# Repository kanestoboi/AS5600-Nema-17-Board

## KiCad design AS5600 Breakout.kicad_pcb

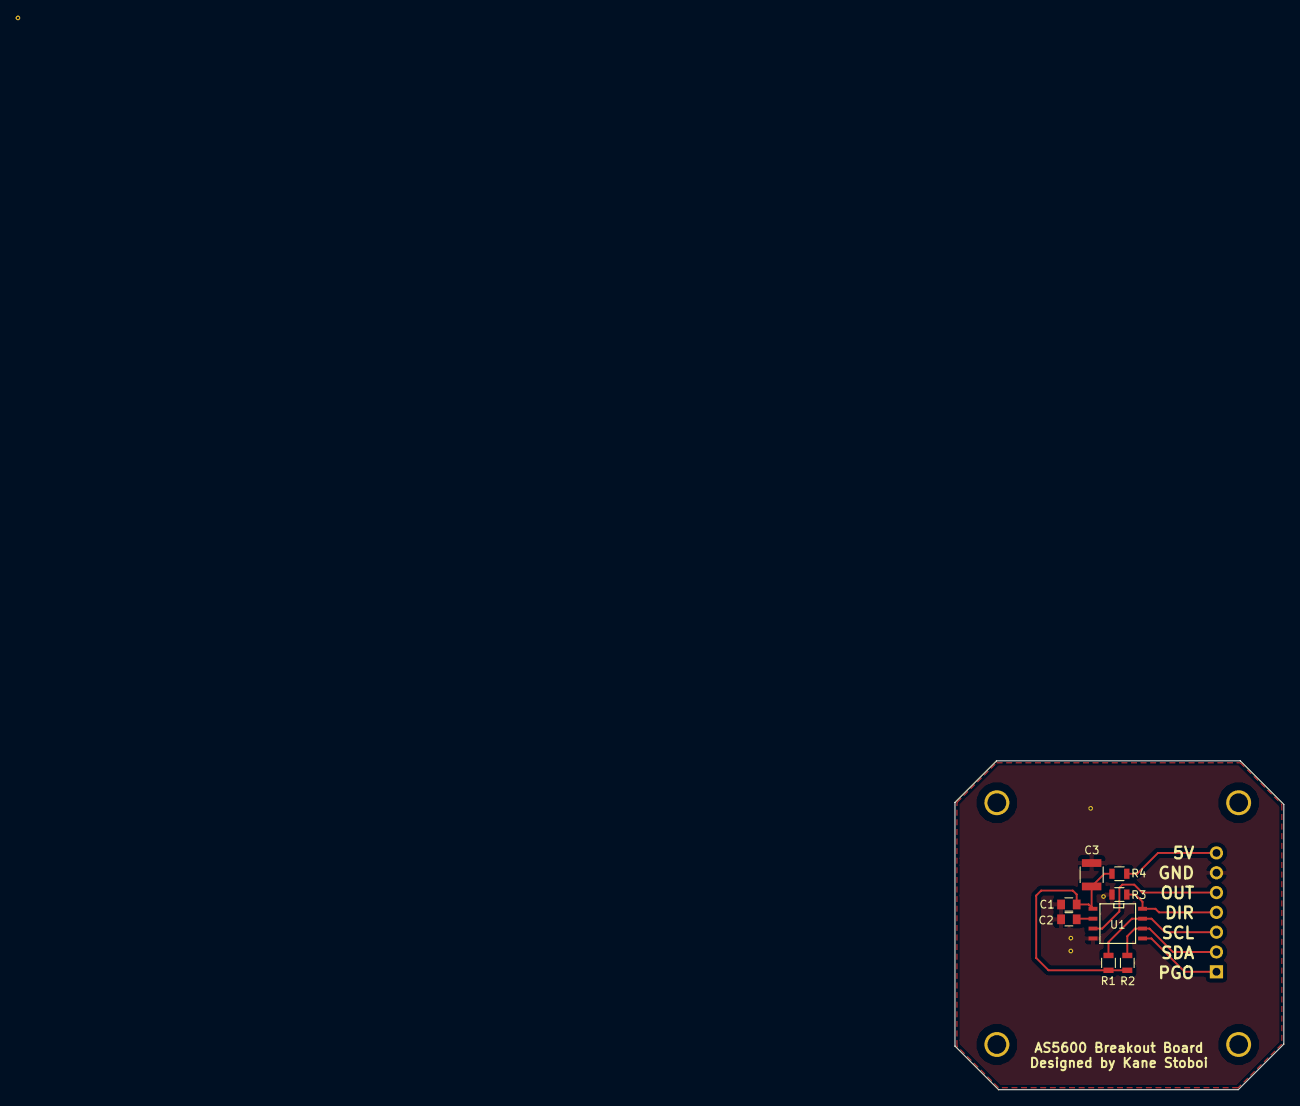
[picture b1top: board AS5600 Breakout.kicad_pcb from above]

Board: 2 copper layers, 42.2 x 42.2 mm, 9 parts (1 on the bottom side), 9 nets.

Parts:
C1: 1uF; C_0805
C2: 100nF; C_0805
C3: 100uF; C_1210
J1: Conn_01x07; Pin_Header_Angled_1x07_Pitch2.54mm
R1, R2: 4.7k; R_0805
R3: R; R_0805
R4: 1.6k; R_0805
U1: AS5600; SOIC-8-N

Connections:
3.3V: C1.2, U1.2
5V: C2.1, C3.2, R1.1, R2.2, R4.1, U1.1
DIR: J1.4, R3.2, U1.8
GND: C1.1, C2.2, C3.1, J1.6, R3.1, U1.4
OUT: J1.5, U1.3
PGO: J1.1, U1.5
SCL: J1.3, R1.2, U1.7
SDA: J1.2, R2.1, U1.6
VIN: J1.7, R4.2

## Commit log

2019-03-09 Adding KiCAD schematic, board layout, and images
2019-03-09 Added schematic image file
2019-03-09 updated schematic symbols
2019-03-09 updating symbols
2019-03-09 Added AS5600 symbol
2019-03-09 Delete AS5600 Breakout-cache.lib
    removed cache file
